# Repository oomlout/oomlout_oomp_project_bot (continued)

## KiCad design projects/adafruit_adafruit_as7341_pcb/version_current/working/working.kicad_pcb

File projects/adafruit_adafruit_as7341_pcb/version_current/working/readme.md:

# Adafruit-AS7341-PCB by adafruit  
This is a harvested standardized copy of a project from github.  
The original project can be found at:  
https://github.com/adafruit/Adafruit-AS7341-PCB  
Please consult that link for additional, details, files, and license information.  
Note: It was auto harvested and if the original repo had more than one board file or anything out of the ordinary the files here are likely not representative.

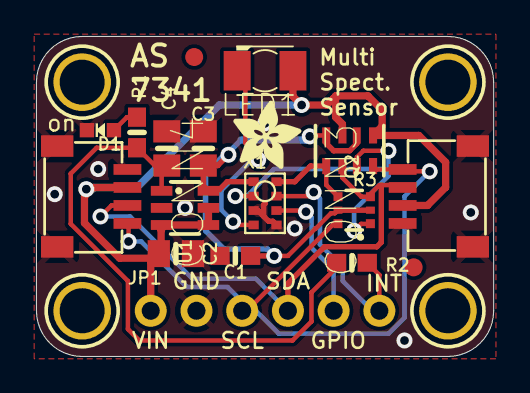
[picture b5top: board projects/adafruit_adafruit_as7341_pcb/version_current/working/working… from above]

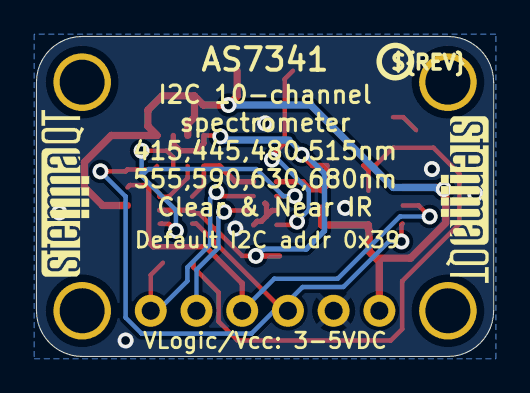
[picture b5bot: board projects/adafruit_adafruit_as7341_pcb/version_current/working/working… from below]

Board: 2 copper layers, 25.4 x 17.8 mm, 25 parts (3 on the bottom side), 12 nets.

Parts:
C1: 0.1uF; 0603-NO
C2, C3, C4: 10uF; 0805-NO
CONN3, CONN4: STEMMA_I2C_QT; JST_SH4
D1: GREEN; CHIPLED_0603_NOOUTLINE
FID3, FID4: FIDUCIAL_1MM
JP1: 1X06_ROUND_70
LED1: EAHC2835WD6; KA-3528ASYC
Q2: BSS138; SOT363
R1, R2: 10K; 0603-NO
R3: 10K; RESPACK_4X0603
U1: AP7312-3.3/1.8; SOT23-6
U$1, U$17, U$19, U$21: MOUNTINGHOLE2.5; MOUNTINGHOLE_2.5_PLATED
U$22: ADAFRUIT_3.5MM
U$25: PCBFEAT-REV-040
U$30, U$31: STEMMAQT
X1: AS7341

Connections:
1.8V: C1.1, C3.1, Q2.2, Q2.5, R3.2, R3.4, U1.6, X1.1
3.3V: C4.1, R1.1, R2.1, U1.1
GND: C1.2, C2.2, C3.2, C4.2, CONN3.1, CONN3.MT1, CONN3.MT2, CONN4.1, CONN4.MT1, CONN4.MT2, D1.C, JP1.2, U1.2, X1.3, X1.5
GPIO: JP1.5, X1.6
INT: JP1.6, R2.2, X1.7
LDR: LED1.C, X1.4
unnamed: D1.A, R1.2
SCL: CONN3.4, CONN4.4, JP1.3, Q2.6, R3.8
SCL_2V: Q2.1, R3.7, X1.2
SDA: CONN3.3, CONN4.3, JP1.4, Q2.3, R3.6
SDA_2V: Q2.4, R3.5, X1.8
VCC: C2.1, CONN3.2, CONN4.2, JP1.1, LED1.A, R3.1, R3.3, U1.3, U1.4, U1.5

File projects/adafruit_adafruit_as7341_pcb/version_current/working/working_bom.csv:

Row,Description,Part,References,Value,Footprint,Quantity Per PCB,Status,Datasheet
1,,CAP_CERAMIC0603_NO,C1,0.1uF,0603-NO,1, ,
2,,CAP_CERAMIC0805-NOOUTLINE,C2 C3 C4,10uF,0805-NO,3, ,
3,,STEMMA_I2C_QT,CONN3 CONN4,STEMMA_I2C_QT,JST_SH4,2, ,
4,,LED0603_NOOUTLINE,D1,GREEN,CHIPLED_0603_NOOUTLINE,1, ,
5,,HEADER-1X670MIL,JP1,HEADER-1X670MIL,1X06_ROUND_70,1, ,
6,,LEDKA-3528ASYC,LED1,EAHC2835WD6,KA-3528ASYC,1, ,
7,,MOSFET-N_DUAL,Q2,BSS138,SOT363,1, ,
8,,RESISTOR_0603_NOOUT,R1 R2,10K,0603-NO,2, ,
9,,RESISTOR_4PACK,R3,10K,RESPACK_4X0603,1, ,
10,,VREG_SOT23-6_DUALAP7312,U1,AP7312-3.3/1.8,SOT23-6,1, ,
11,,AS7341,X1,AS7341,AS7341,1, ,





Project info:
Schematic:,working
Variant:,default
Revision:,
Date:,2023-08-02_17-08-32
KiCad Version:,7.0.6-7.0.6~ubuntu22.04.1
Statistics:
Component Groups:,11
Component Count:,15 (0 SMD/ 0 THT)
Fitted Components:,15 (0 SMD/ 0 THT)
Number of PCBs:,1
Total Components:,15

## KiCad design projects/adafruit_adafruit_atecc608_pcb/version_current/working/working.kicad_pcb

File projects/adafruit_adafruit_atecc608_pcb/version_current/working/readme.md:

# OOMP Project  
## Adafruit-ATECC608-PCB  by adafruit  
  
oomp key: oomp_projects_flat_adafruit_adafruit_atecc608_pcb  
(snippet of original readme)  
  
-- Adafruit Adafruit ATECC608 Breakout Board - STEMMA QT / Qwiic PCB  
  
<a href="http://www.adafruit.com/products/4314"><br/>  
Click here to purchase one from the Adafruit shop</a>  
  
PCB files for the Adafruit Adafruit ATECC608 Breakout Board - STEMMA QT / Qwiic.   
  
Format is EagleCAD schematic and board layout  
* https://www.adafruit.com/product/4314  
  
--- Description  
  
You've got secrets, and you want to keep them safe? Most microcontrollers are not designed to protect against snoopers, but a crypto-authentication chip can be used to lock away private keys securely. Once the private key is saved inside, it can't be read out, all you can do is send it challenge-response queries. That means that even if someone gets hold of your hardware and can read back the firmware, they wont be able to extract the secret!  
  
The ATECC608 is the latest crypto-auth chip from Microchip, and it uses I2C to send/receive commands. Once you 'lock' the chip with your details, you can use it for ECDH and AES-128 encrypt/decrypt/signing. There's also hardware support for random number generation, and SHA-256/HMAC hash functions to  greatly speed up a slower micro's cryptography commands.  
  
--- License  
  
Adafruit invests time and resources providing this open source design, please support Adafruit and open-source hardware by purchasing products from [Adafruit](https://www.adafruit.com)!  
  
Designed by Limor Fried/Ladyada for Adafruit Industries.  
  
Creative Commons   
  full source readme at [readme_src.md](readme_src.md)  
  
source repo at: [https://github.com/adafruit/Adafruit-ATECC608-PCB](https://github.com/adafruit/Adafruit-ATECC608-PCB)  
## Board  

## Schematic  

[schematic pdf](working_schematic.pdf)  
## Images

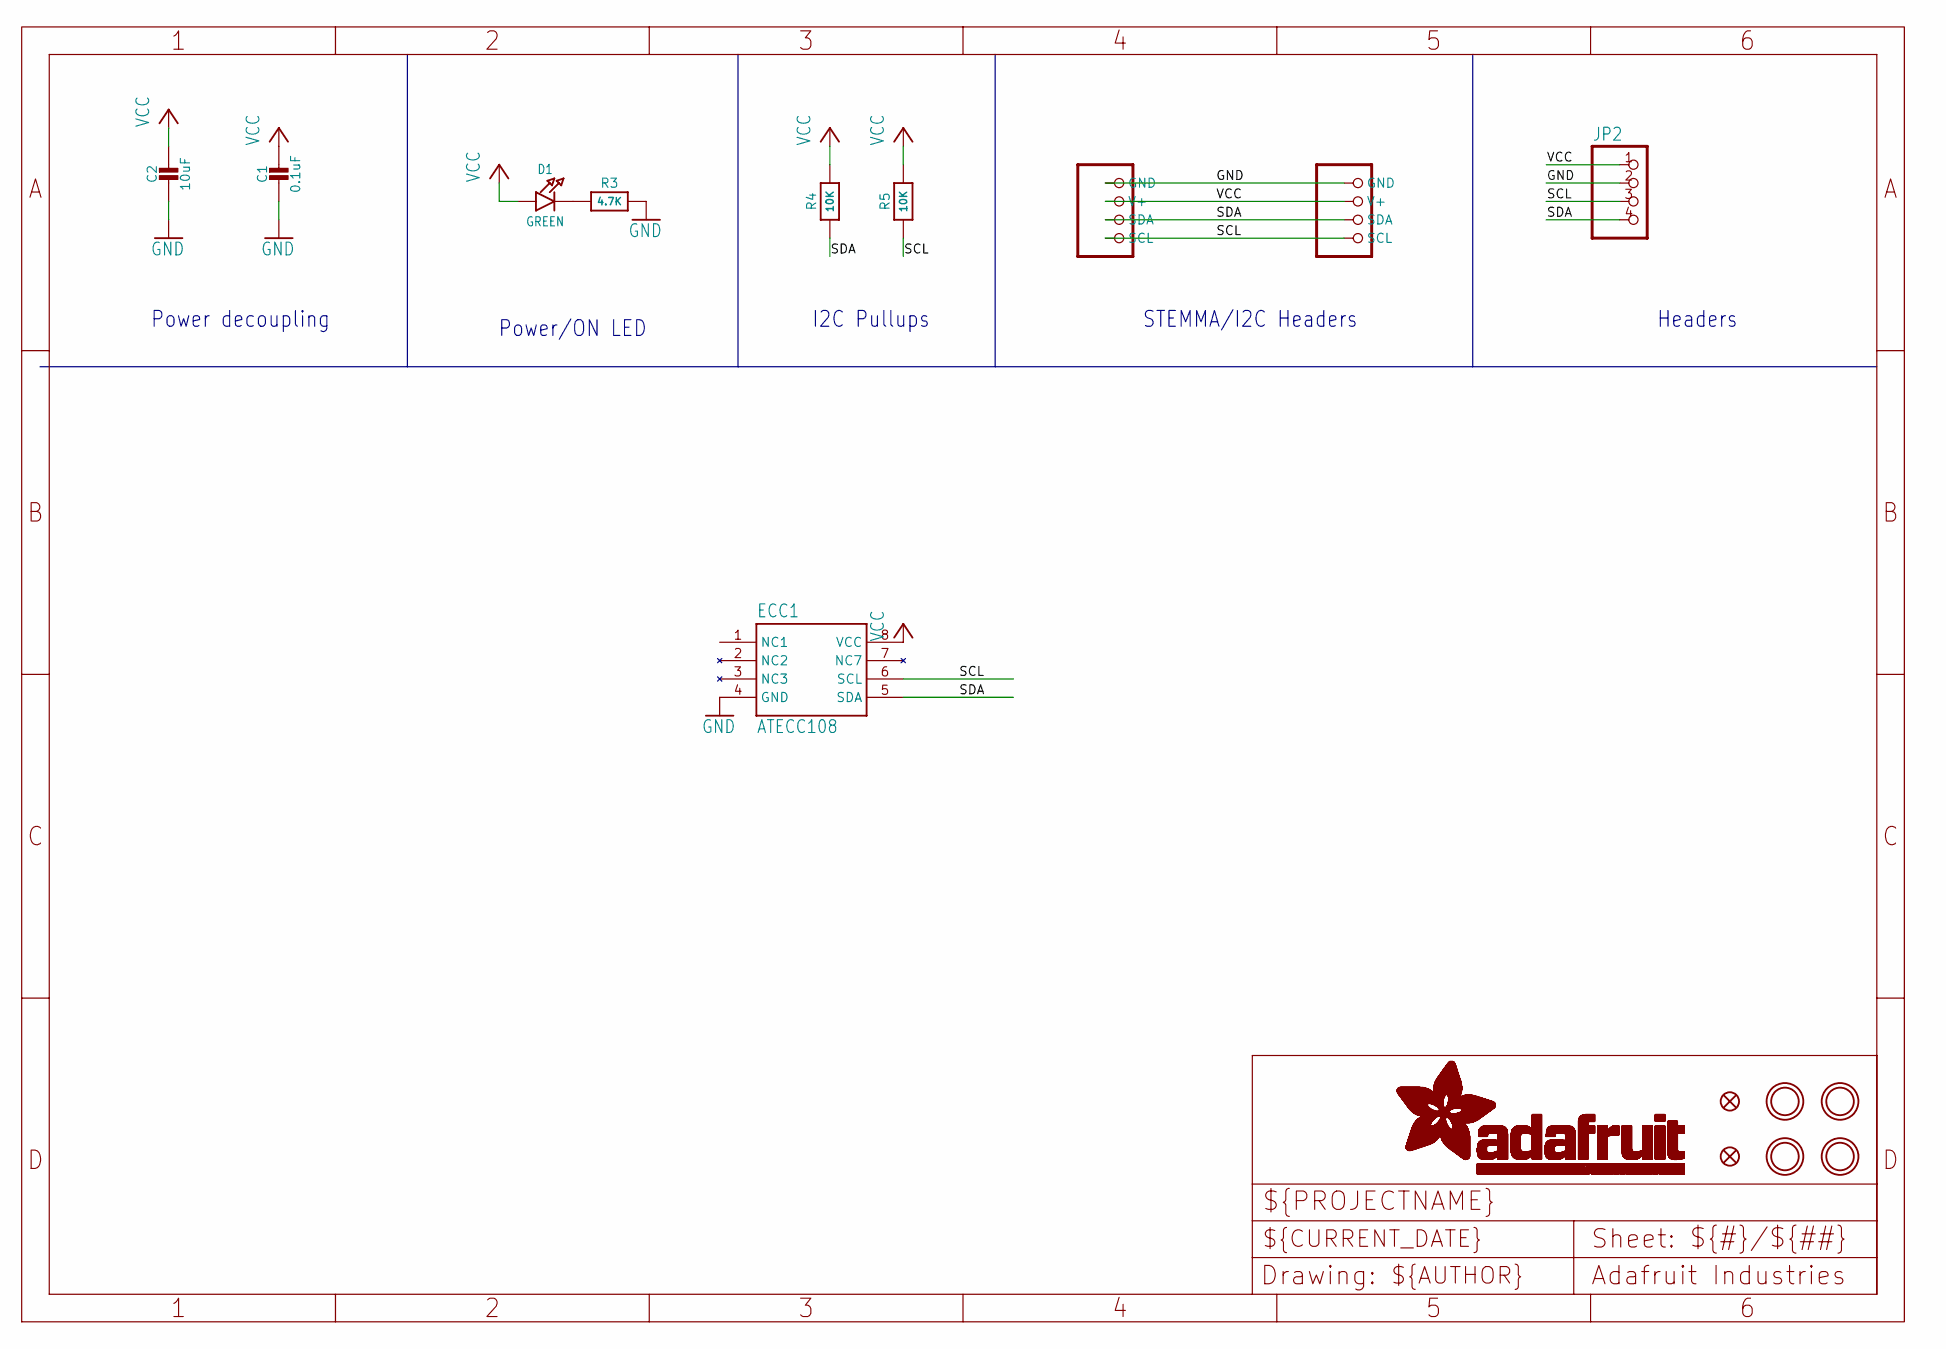
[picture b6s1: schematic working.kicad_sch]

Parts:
C1: 0.1uF; 0603-NO
C2: 10uF; 0805-NO
CONN3, CONN4: STEMMA_I2C_QT; JST_SH4
D1: GREEN; CHIPLED_0603_NOOUTLINE
ECC1: ATECC108; SOIC8
FID3, FID4: FIDUCIAL_1MM
JP2: HEADER-1X4ROUND; 1X04_ROUND
R3: 4.7K; 0603-NO
R4, R5: 10K; 0603-NO
U$11, U$12, U$14, U$15: MOUNTINGHOLE2.5; MOUNTINGHOLE_2.5_PLATED

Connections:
GND: C1.2, C2.2, CONN3.1 (GND), CONN4.1 (GND), ECC1.4 (GND), JP2.2, R3.2
unnamed: D1.C, R3.1
SCL: CONN3.4 (SCL), CONN4.4 (SCL), ECC1.6 (SCL), JP2.3, R5.1
SDA: CONN3.3 (SDA), CONN4.3 (SDA), ECC1.5 (SDA), JP2.4, R4.1
VCC: C1.1, C2.1, CONN3.2 (V+), CONN4.2 (V+), D1.A, ECC1.8 (VCC), JP2.1, R4.2, R5.2

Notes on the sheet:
Power decoupling
Headers
Power/ON LED
I2C Pullups
STEMMA/I2C Headers

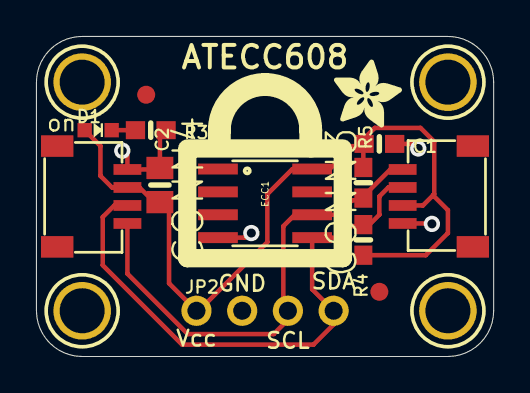
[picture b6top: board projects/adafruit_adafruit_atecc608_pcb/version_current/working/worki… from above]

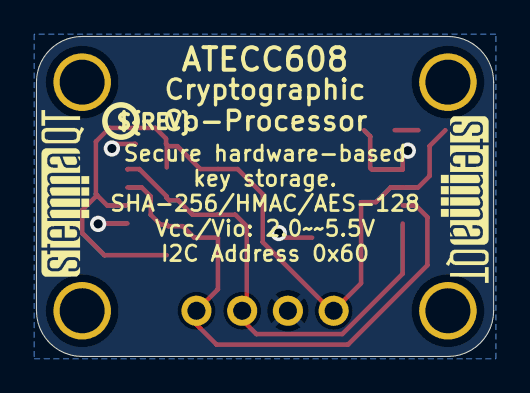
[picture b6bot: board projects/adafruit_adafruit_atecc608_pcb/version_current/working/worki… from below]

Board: 2 copper layers, 25.4 x 17.8 mm, 20 parts (3 on the bottom side), 5 nets.

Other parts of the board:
U$17: ADAFRUIT_3.5MM
U$18: PCBFEAT-REV-040
U$19, U$20: STEMMAQT

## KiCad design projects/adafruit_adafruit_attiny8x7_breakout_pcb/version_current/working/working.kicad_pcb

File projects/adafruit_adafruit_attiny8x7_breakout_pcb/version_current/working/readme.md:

# OOMP Project  
## Adafruit-ATtiny8x7-Breakout-PCB  by adafruit  
  
oomp key: oomp_projects_flat_adafruit_adafruit_attiny8x7_breakout_pcb  
(snippet of original readme)  
  
-- Adafruit ATtiny8x7 Breakout PCB  
  
<a href="http://www.adafruit.com/products/5233"><br/>  
Click here to purchase one from the Adafruit shop</a>  
  
PCB files for the Adafruit ATtiny8x7 Breakout.   
  
Format is EagleCAD schematic and board layout  
* https://www.adafruit.com/product/5233  
  
--- Description  
  
This breakout board is a "three in one" product:  
  
1. The ATtiny817 is part of the 'next gen' of AVR microcontrollers, and now we have a cute development/breakout board for it, with just enough hardware to get the chip up and running.  
2. It's also an Adafruit seesaw board. Adafruit seesaw is a near-universal converter framework which allows you to add and extend hardware support to any I2C-capable microcontroller or microcomputer. Instead of getting separate I2C GPIO expanders, ADCs, PWM drivers, etc, seesaw can be configured to give a wide range of capabilities.  
3. Finally, with STEMMA QT connectors on it, you could use it as either an I2C controller or peripheral with plug-and play support.  
  
We primarily designed this board for our own use: it's a mini dev board that lets us design with the ATtiny817 just like we did for the ATSAMD09. With the 2021 silicon shortage, we're adapting some of our SAMD09 designs to the ATTiny8xx series and wanted a quick minimal board to test code on.  
  
Each breakout comes with the assembled and tested board, as well as some header strips. Each PCB is fairly minimal and contains:  
  
* ATtiny817 8-bit microco  
  full source readme at [readme_src.md](readme_src.md)  
  
source repo at: [https://github.com/adafruit/Adafruit-ATtiny8x7-Breakout-PCB](https://github.com/adafruit/Adafruit-ATtiny8x7-Breakout-PCB)  
## Board  

## Schematic  

[schematic pdf](working_schematic.pdf)  
## Images

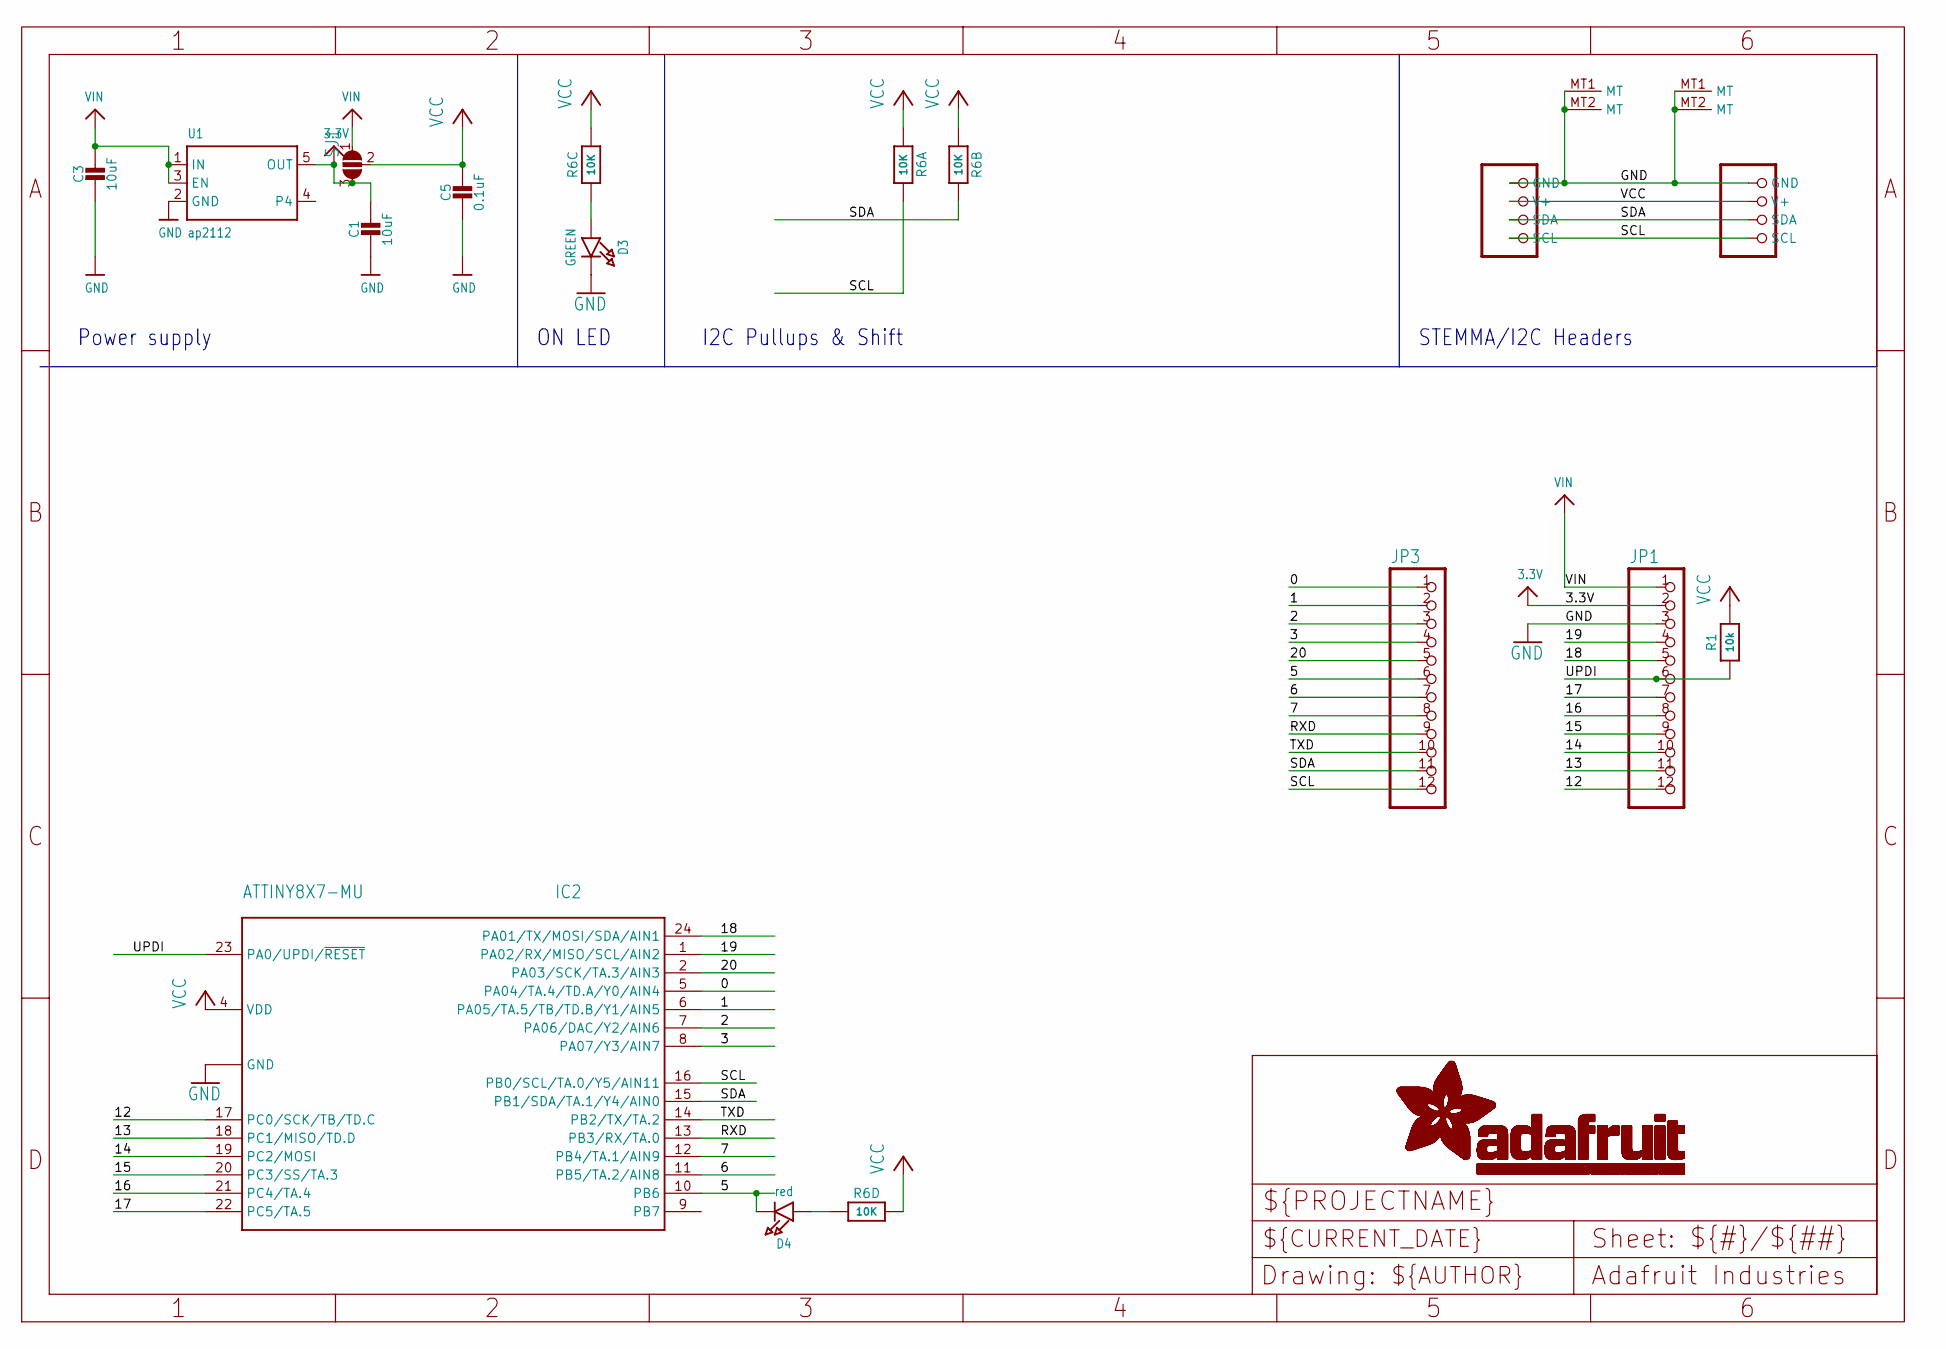
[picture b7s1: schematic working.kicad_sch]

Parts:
C1: 10uF; 0805_10MGAP
C3: 10uF; 0805-NO
C5: 0.1uF; 0603-NO
CONN3, CONN4: STEMMA_I2C_QT; JST_SH4
D3: GREEN; CHIPLED_0603_NOOUTLINE
D4: red; CHIPLED_0603_NOOUTLINE
IC2: ATTINY8X7-MU; QFN24_4MM
JP1, JP3: HEADER-1X1276MIL; 1X12_ROUND_76MIL
R1: 10k; 0603-NO
R6: 10K; RESPACK_4X0603
SJ1: SOLDERJUMPER_2WAY; SOLDERJUMPER_2WAY_OPEN_NOPASTE
U1: ap2112; SOT23-5

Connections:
0: IC2.5 (PA04/TA.4/TD.A/Y0/AIN4), JP3.1
1: IC2.6 (PA05/TA.5/TB/TD.B/Y1/AIN5), JP3.2
2: IC2.7 (PA06/DAC/Y2/AIN6), JP3.3
3: IC2.8 (PA07/Y3/AIN7), JP3.4
3.3V: C1.1, JP1.2, SJ1.3, U1.5 (OUT)
5: D4.C, IC2.10 (PB6), JP3.6
6: IC2.11 (PB5/TA.2/AIN8), JP3.7
7: IC2.12 (PB4/TA.1/AIN9), JP3.8
12: IC2.17 (PC0/SCK/TB/TD.C), JP1.12
13: IC2.18 (PC1/MISO/TD.D), JP1.11
14: IC2.19 (PC2/MOSI), JP1.10
15: IC2.20 (PC3/SS/TA.3), JP1.9
16: IC2.21 (PC4/TA.4), JP1.8
17: IC2.22 (PC5/TA.5), JP1.7
18: IC2.24 (PA01/TX/MOSI/SDA/AIN1), JP1.5
19: IC2.1 (PA02/RX/MISO/SCL/AIN2), JP1.4
20: IC2.2 (PA03/SCK/TA.3/AIN3), JP3.5
GND: C1.2, C3.2, C5.2, CONN3.1 (GND), CONN3.MT1 (MT), CONN3.MT2 (MT), CONN4.1 (GND), CONN4.MT1 (MT), CONN4.MT2 (MT), D3.C, IC2.3 (GND), IC2.THERM (GND), JP1.3, U1.2 (GND)
unnamed: D3.A, R6.3 (1)
unnamed: D4.A, R6.4 (1)
RXD: IC2.13 (PB3/RX/TA.0), JP3.9
SCL: CONN3.4 (SCL), CONN4.4 (SCL), IC2.16 (PB0/SCL/TA.0/Y5/AIN11), JP3.12, R6.8 (2)
SDA: CONN3.3 (SDA), CONN4.3 (SDA), IC2.15 (PB1/SDA/TA.1/Y4/AIN0), JP3.11, R6.7 (2)
TXD: IC2.14 (PB2/TX/TA.2), JP3.10
UPDI: IC2.23 (PA0/UPDI/~RESET), JP1.6, R1.1
VCC: C5.1, CONN3.2 (V+), CONN4.2 (V+), IC2.4 (VDD), R1.2, R6.1, R6.2 (1), R6.5 (2), R6.6 (2), SJ1.2
VIN: C3.1, JP1.1, SJ1.1, U1.1 (IN), U1.3 (EN)

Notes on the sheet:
I2C Pullups & Shift
Power supply
ON LED
STEMMA/I2C Headers

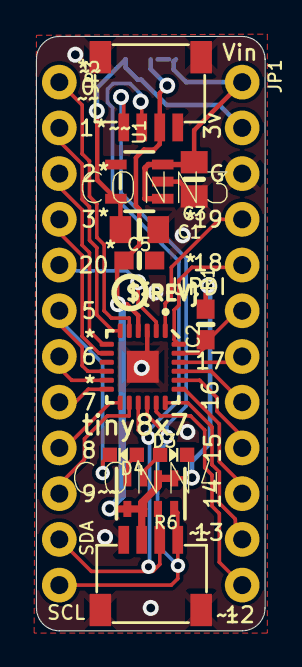
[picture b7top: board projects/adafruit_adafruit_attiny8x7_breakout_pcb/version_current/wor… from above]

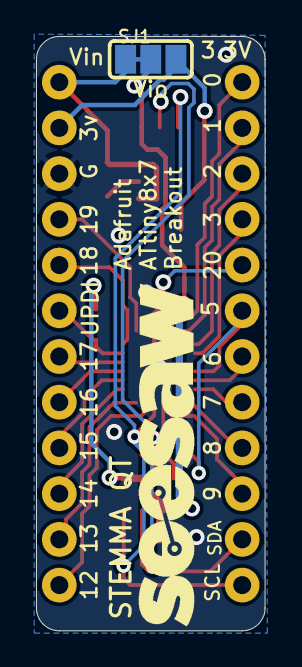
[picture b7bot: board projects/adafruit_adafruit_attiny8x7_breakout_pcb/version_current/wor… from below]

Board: 2 copper layers, 12.7 x 33.0 mm, 16 parts (2 on the bottom side), 27 nets.

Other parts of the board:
U$7: SEESAW_LOGO
U$12: PCBFEAT-REV-040

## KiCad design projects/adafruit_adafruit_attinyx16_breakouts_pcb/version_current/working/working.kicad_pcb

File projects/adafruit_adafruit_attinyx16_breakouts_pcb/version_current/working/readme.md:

# OOMP Project  
## Adafruit-ATtinyx16-Breakouts-PCB  by adafruit  
  
oomp key: oomp_projects_flat_adafruit_adafruit_attinyx16_breakouts_pcb  
(snippet of original readme)  
  
-- Adafruit ATtinyx16 Breakouts with seesaw - STEMMA QT / Qwiic PCB  
  
<a href="http://www.adafruit.com/products/5681"><br/>  
Click here to purchase one from the Adafruit shop</a>  
<a href="http://www.adafruit.com/products/5690"><br/>  
Click here to purchase one from the Adafruit shop</a>  
  
PCB files for the Adafruit ATtiny816 and ATtiny1616 Breakouts with seesaw - STEMMA QT / Qwiic.   
  
Format is EagleCAD schematic and board layout  
* https://www.adafruit.com/product/5681  
* https://www.adafruit.com/product/5690  
  
--- Description  
  
These breakout boards are a "three in one" product:  
  
* The ATtinyx16 are part of the 'next gen' of AVR microcontrollers, and now we have cute development/breakout boards for them, with just enough hardware to get the chip up and running.  
* It's also an Adafruit seesaw board. Adafruit seesaw is a near-universal converter framework which allows you to add and extend hardware support to any I2C-capable microcontroller or microcomputer. Instead of getting separate I2C GPIO expanders, ADCs, PWM drivers, etc, seesaw can be configured to give a wide range of capabilities.  
* Finally, with STEMMA QT connectors on it, you could use it as either an I2C controller or peripheral with plug-and play support.  
  
We primarily designed this board for our own use: it's a mini dev board that lets us design with the ATtiny816 just like we did for the ATSAMD09. With the 2021-202  
  full source readme at [readme_src.md](readme_src.md)  
  
source repo at: [https://github.com/adafruit/Adafruit-ATtinyx16-Breakouts-PCB](https://github.com/adafruit/Adafruit-ATtinyx16-Breakouts-PCB)  
## Board  

## Schematic  

[schematic pdf](working_schematic.pdf)  
## Images

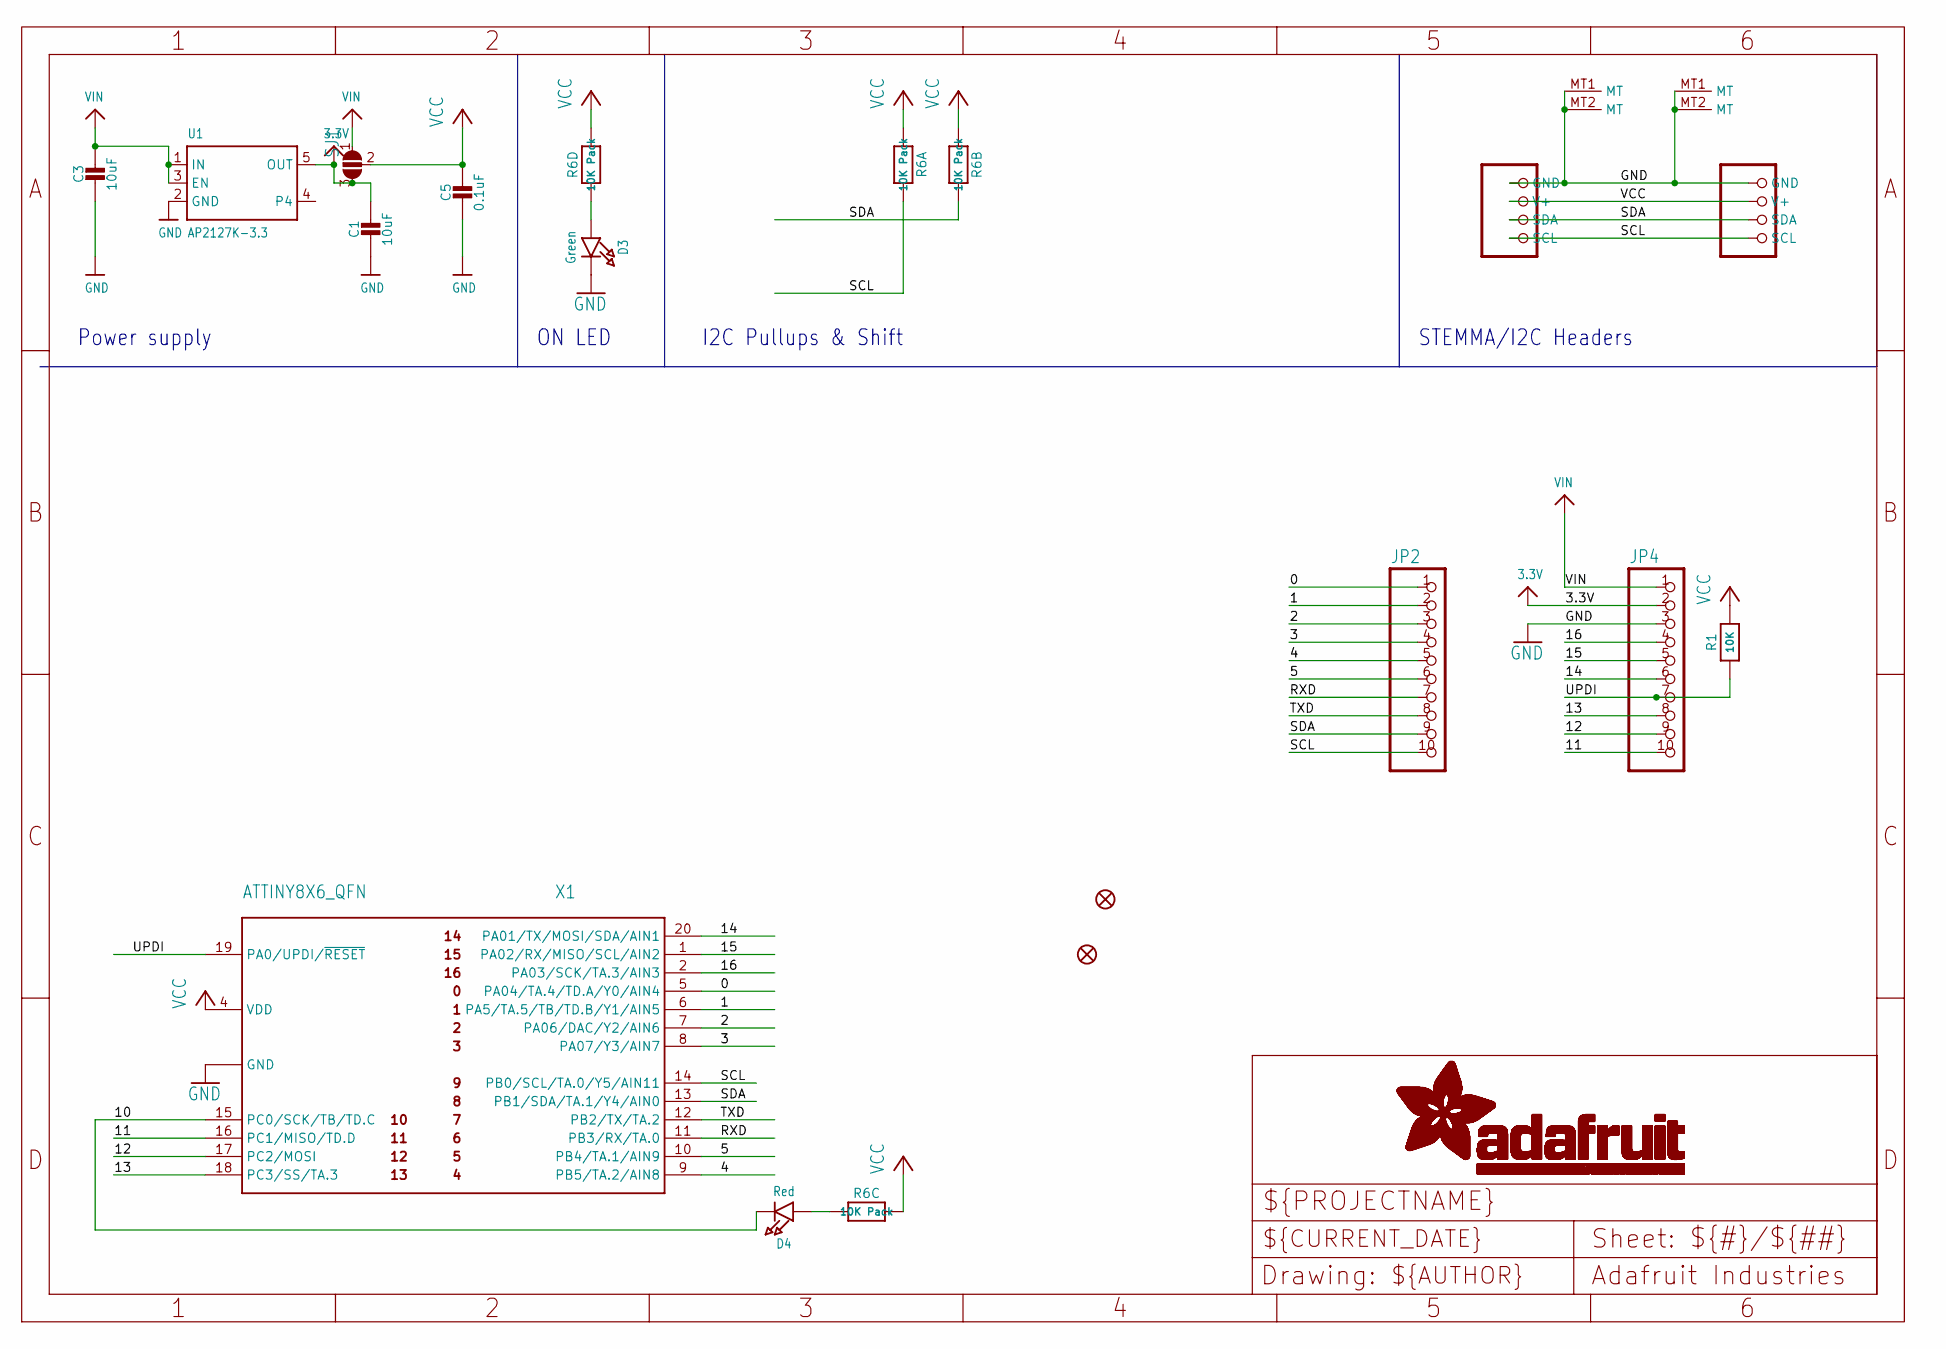
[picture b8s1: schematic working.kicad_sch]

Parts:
C1: 10uF; 0805_10MGAP
C3: 10uF; 0805-NO
C5: 0.1uF; 0603-NO
CONN3, CONN4: STEMMA_I2C_QT; JST_SH4
D3: Green; CHIPLED_0603_NOOUTLINE
D4: Red; CHIPLED_0603_NOOUTLINE
FID1, FID2: FIDUCIAL_1MM
JP2, JP4: HEADER-1X1070MIL; 1X10_ROUND70
R1: 10K; 0603-NO
R6: 10K Pack; RESPACK_4X0603
SJ1: SOLDERJUMPER_2WAY; SOLDERJUMPER_2WAY_OPEN_NOPASTE
U1: AP2127K-3.3; SOT23-5
X1: ATTINY8X6_QFN; QFN20_3MM

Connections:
0: JP2.1, X1.5 (PA04/TA.4/TD.A/Y0/AIN4)
1: JP2.2, X1.6 (PA5/TA.5/TB/TD.B/Y1/AIN5)
2: JP2.3, X1.7 (PA06/DAC/Y2/AIN6)
3: JP2.4, X1.8 (PA07/Y3/AIN7)
3.3V: C1.1, JP4.2, SJ1.3, U1.5 (OUT)
4: JP2.5, X1.9 (PB5/TA.2/AIN8)
5: JP2.6, X1.10 (PB4/TA.1/AIN9)
10: D4.C, X1.15 (PC0/SCK/TB/TD.C)
11: JP4.10, X1.16 (PC1/MISO/TD.D)
12: JP4.9, X1.17 (PC2/MOSI)
13: JP4.8, X1.18 (PC3/SS/TA.3)
14: JP4.6, X1.20 (PA01/TX/MOSI/SDA/AIN1)
15: JP4.5, X1.1 (PA02/RX/MISO/SCL/AIN2)
16: JP4.4, X1.2 (PA03/SCK/TA.3/AIN3)
GND: C1.2, C3.2, C5.2, CONN3.1 (GND), CONN3.MT1 (MT), CONN3.MT2 (MT), CONN4.1 (GND), CONN4.MT1 (MT), CONN4.MT2 (MT), D3.C, JP4.3, U1.2 (GND), X1.3 (GND), X1.PAD (GND)
unnamed: D3.A, R6.4 (1)
unnamed: D4.A, R6.3 (1)
RXD: JP2.7, X1.11 (PB3/RX/TA.0)
SCL: CONN3.4 (SCL), CONN4.4 (SCL), JP2.10, R6.8 (2), X1.14 (PB0/SCL/TA.0/Y5/AIN11)
SDA: CONN3.3 (SDA), CONN4.3 (SDA), JP2.9, R6.7 (2), X1.13 (PB1/SDA/TA.1/Y4/AIN0)
TXD: JP2.8, X1.12 (PB2/TX/TA.2)
UPDI: JP4.7, R1.1, X1.19 (PA0/UPDI/~RESET)
VCC: C5.1, CONN3.2 (V+), CONN4.2 (V+), R1.2, R6.1, R6.2 (1), R6.5 (2), R6.6 (2), SJ1.2, X1.4 (VDD)
VIN: C3.1, JP4.1, SJ1.1, U1.1 (IN), U1.3 (EN)

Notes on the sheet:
STEMMA/I2C Headers
ON LED
I2C Pullups & Shift
Power supply

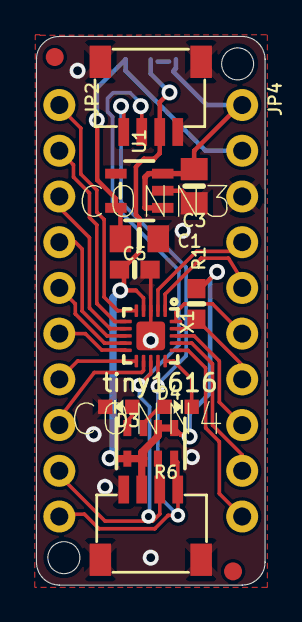
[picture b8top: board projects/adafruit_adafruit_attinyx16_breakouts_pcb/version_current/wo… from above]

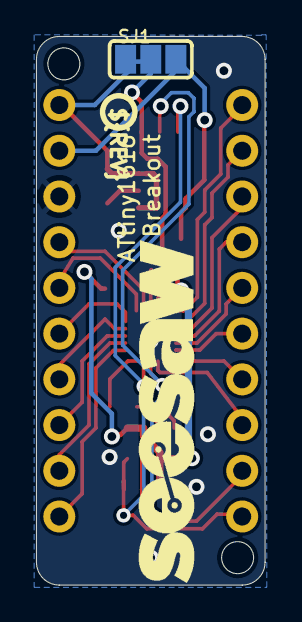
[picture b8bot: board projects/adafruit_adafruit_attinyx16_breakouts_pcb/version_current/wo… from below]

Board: 2 copper layers, 12.7 x 30.5 mm, 77 parts (27 on the bottom side), 24 nets.

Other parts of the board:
@HOLE0, @HOLE1: (no value)
PLABEL0: PLABEL0
PLABEL1: PLABEL1
PLABEL2: PLABEL2
PLABEL3: PLABEL3
PLABEL4: PLABEL4
PLABEL5: PLABEL5
PLABEL6: PLABEL6
PLABEL7: PLABEL7
PLABEL8: PLABEL8
PLABEL9: PLABEL9
PLABEL10: PLABEL10
PLABEL11: PLABEL11
PLABEL12: PLABEL12
PLABEL13: PLABEL13
PLABEL14: PLABEL14
PLABEL15: PLABEL15
PLABEL17: PLABEL17
PLABEL18: PLABEL18
PLABEL19: PLABEL19
PLABEL20: PLABEL20
PLABEL21: PLABEL21
PLABEL22: PLABEL22
PLABEL23: PLABEL23
PLABEL24: PLABEL24
PLABEL25: PLABEL25
PLABEL26: PLABEL26
PLABEL27: PLABEL27
PLABEL28: PLABEL28
PLABEL29: PLABEL29
PLABEL30: PLABEL30
PLABEL31: PLABEL31
PLABEL32: PLABEL32
PLABEL33: PLABEL33
PLABEL35: PLABEL35
PLABEL36: PLABEL36
PLABEL37: PLABEL37
PLABEL38: PLABEL38
PLABEL39: PLABEL39
PLABEL40: PLABEL40
PLABEL41: PLABEL41
PLABEL42: PLABEL42
PLABEL43: PLABEL43
PLABEL44: PLABEL44
PLABEL45: PLABEL45
PLABEL46: PLABEL46
PLABEL47: PLABEL47
PLABEL48: PLABEL48
PLABEL49: PLABEL49
PLABEL50: PLABEL50
PLABEL51: PLABEL51
PLABEL52: PLABEL52
PLABEL53: PLABEL53
PLABEL54: PLABEL54
PLABEL55: PLABEL55
PLABEL56: PLABEL56
PLABEL57: PLABEL57
PLABEL58: PLABEL58
U$7: SEESAW_LOGO
U$12: PCBFEAT-REV-040
